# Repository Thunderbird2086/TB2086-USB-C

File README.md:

# TB2086 USB-C Breakout Board

A compact USB-C breakout board designed for keyboard projects. This repository contains KiCad design files, production outputs, and documentation for the TB2086-USB-C panelized PCB.

## Features
* USB-C receptacle for modern connectivity
* 1.5U size for keyboard compatibility

## Bill of Materials (BOM)

| Comment                | Designator   | Footprint                                         | LCSC         | Quantity |
|------------------------|--------------|---------------------------------------------------|--------------|----------|
| 4.7n                   | C1           | C_0805_2012Metric                                 | C16036       | 1        |
| 10u                    | C2           | C_0603_1608Metric                                 | C19702       | 1        |
| 500mA                  | F1           | Fuse_0805_2012Metric                              | C66452       | 1        |
| 1M                     | R1           | R_0603_1608Metric_Pad0.98x0.95mm_HandSolder       |              | 1        |
| 5K1                    | R2, R3       | R_0603_1608Metric_Pad0.98x0.95mm_HandSolder       | C22356620    | 2        |
| USBLC6-2SC6            | U1           | SOT-23-6                                          | C2827654     | 1        |
| Conn_01x04             | J1           | Molex_Pico-EZmate_78171-0004_1x04-1MP_P1.                        | 1        |
| USB_C_Receptacle_USB2.0_16P | USB1    | TYPE-C-31-M-14_HRO (mid mount)                    |              | 1        |

## Assembly Notes
- All footprints are hand-solderable
- Refer to schematic for signal mapping

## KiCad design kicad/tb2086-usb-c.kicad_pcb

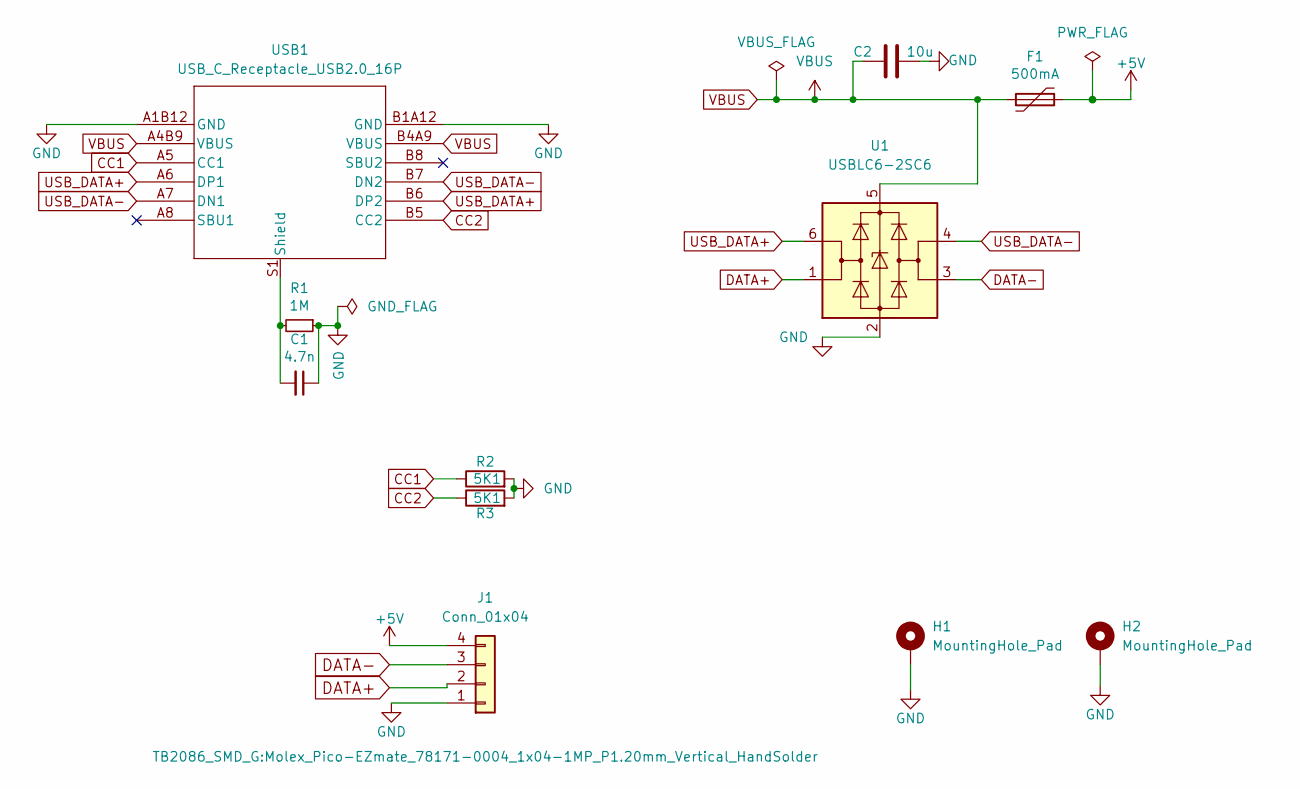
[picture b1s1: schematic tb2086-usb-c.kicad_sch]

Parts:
C1: 4.7n; C_0805_2012Metric; LCSC C16036
C2: 10u; C_0603_1608Metric_Pad1.08x0.95mm_HandSolder; MPN CL10A106KP8NNNC; JLCSMT C19702
F1: 500mA; Fuse_0805_2012Metric_Pad1.15x1.40mm_HandSolder; MPN SMD0805-050; JLCSMT C66452
H1, H2: MountingHole_Pad; MountingHole_3.2mm_M3_Pad_Via
J1: Conn_01x04; Molex_Pico-EZmate_78171-0004_1x04-1MP_P1.20mm_Vertical_Hand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
R1: 1M; R_0603_1608Metric_Pad0.98x0.95mm_HandSolder
R2, R3: 5K1; R_0603_1608Metric_Pad0.98x0.95mm_HandSolder; LCSC C22356620
U1: USBLC6-2SC6; SOT-23-6; LCSC C2827654
USB1: USB_C_Receptacle_USB2.0_16P; TYPE-C-31-M-14_HRO

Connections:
+5V: F1.1, J1.4
CC1: R2.1, USB1.A5 (CC1)
CC2: R3.1, USB1.B5 (CC2)
DATA+: J1.2, U1.1 (I/O1)
DATA-: J1.3, U1.3 (I/O2)
GND: C1.1, C2.1, H1.1, H2.1, J1.1, R1.1, R2.2, R3.2, U1.2 (GND), USB1.A1B12 (GND), USB1.B1A12 (GND)
unnamed: C1.2, R1.2, USB1.S1 (Shield)
USB_DATA+: U1.6 (I/O1), USB1.A6 (DP1), USB1.B6 (DP2)
USB_DATA-: U1.4 (I/O2), USB1.A7 (DN1), USB1.B7 (DN2)
VBUS: C2.2, F1.2, U1.5 (VBUS), USB1.A4B9 (VBUS), USB1.B4A9 (VBUS)

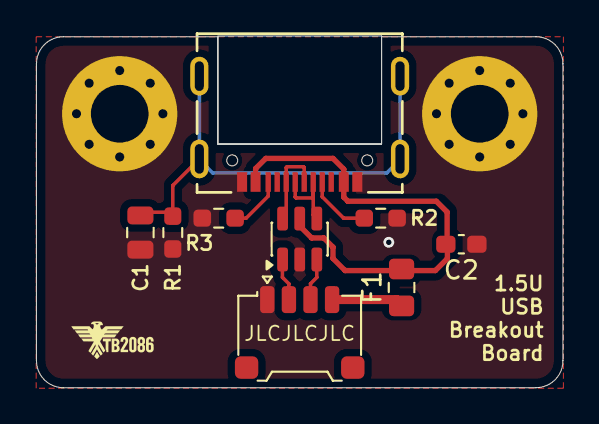
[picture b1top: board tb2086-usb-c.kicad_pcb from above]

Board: 2 copper layers, 29.3 x 19.5 mm, 11 parts (0 on the bottom side), 10 nets.

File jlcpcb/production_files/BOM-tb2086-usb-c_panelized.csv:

Comment,Designator,Footprint,LCSC,Quantity
10u,C2,C_0603_1608Metric,C19702,1
4.7n,C1,C_0805_2012Metric,C16036,1
500mA,F1,Fuse_0805_2012Metric,C66452,1
5K1,"R2,R3",R_0603_1608Metric_Pad0.98x0.95mm_HandSolder,C22356620,2
SRV05-4,U1,SOT-23-6,C85364,1
1M,R1,R_0603_1608Metric_Pad0.98x0.95mm_HandSolder,,1
Conn_01x04,J1,Molex_Pico-EZmate_78171-0004_1x04-1MP_P1.20mm_Vertical_HandSolder,,1
USB_C_Receptacle_USB2.0_16P,USB1,TYPE-C-31-M-14_HRO,,1

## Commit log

2025-11-22 USB-C Breakout Board
2025-11-22 USB-C Breakout Board (#1)
    * USB-C Breakout Board
    * updated README.md
2025-11-22 clean up
2025-11-22 kibot
2025-11-22 kibot (#2)
    * clean up
    * kibot
2025-11-22 fixed kibot
2025-11-22 fixed kibot (#3)
2025-11-22 kibot 1.8.3
2025-11-22 fixed kibot (#4)
    * fixed kibot
    * kibot 1.8.3
2025-11-22 tweak github action
2025-11-22 kibot (#5)
    * fixed kibot
    * kibot 1.8.3
    * tweak github action
2025-11-22 replaced ESD protection
2025-11-23 updated panelized PCB
2025-11-23 fixed zip file name
2025-11-23 changed ESD protection (#6)
    * replaced ESD protection
    * updated panelized PCB
    * kibot
    * fixed zip file name
2025-11-23 changed footprint
2025-11-23 changed footprint (#7)
